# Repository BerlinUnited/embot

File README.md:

# embot
A simple controller kit for robotic experiments in embodyment. 

Some robots build by the students in our Embodied Robotics class:  
https://www.youtube.com/watch?v=9PvMIzAKYXQ

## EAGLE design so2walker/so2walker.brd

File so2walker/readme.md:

# BOM

## PCB mount

| Part  | Value  | Package          | Description    | Order                      |
|-------|--------|------------------|----------------|----------------------------|
| C1    | 100µF  | CPOL-EUE3.5-8    | Elko (Bulk)    | Reichelt, M-A 100U 35      |
| C2    | 100nF  | C-EU025-025X050  | Keramik Cap    | Reichelt, Z5U-2,5 100N     |
| D1,D2 |        | LED3MM           | LED            | -                          |
| R1,R2 | 1K     | R-EU_0207/7      | Resistor       | Reichelt, AG 04FTE52-1K    |
| SW    |        | SWITCH-SPSTPTH   | On/off Switch  | Reichelt, SS ESP101        |
| T1    |        | TAC_SWITCHPTH    | Tactile Switch | Reichelt, RND 210-00193    |
| P1-P4 | 10K    | TRIMPOT_UNIV     | Trimmerpotis   | Reichelt, ACP 9-SRS 10K    |
| M1-M4 |        | PINHD 2.54mm     | Pinheader 1x3  | Reichelt, MPE 087-1-003    |

Also needed:

* Arduino-Nano (or compatible)
* 2x Sockets 2.54 mm, 1X15, straight (if Arduino Nano shall not be permanently soldered)
* 2x Battery-Holder (e.g. Reichelt, HALTER 2XAAZ) + 4x AA Battery
* 4x Knob for Pots: e.g. Reichelt, ACHSE ACP 9 S
* 2-4x Micro-Servo: e.g. Conrad, 275460 - 62

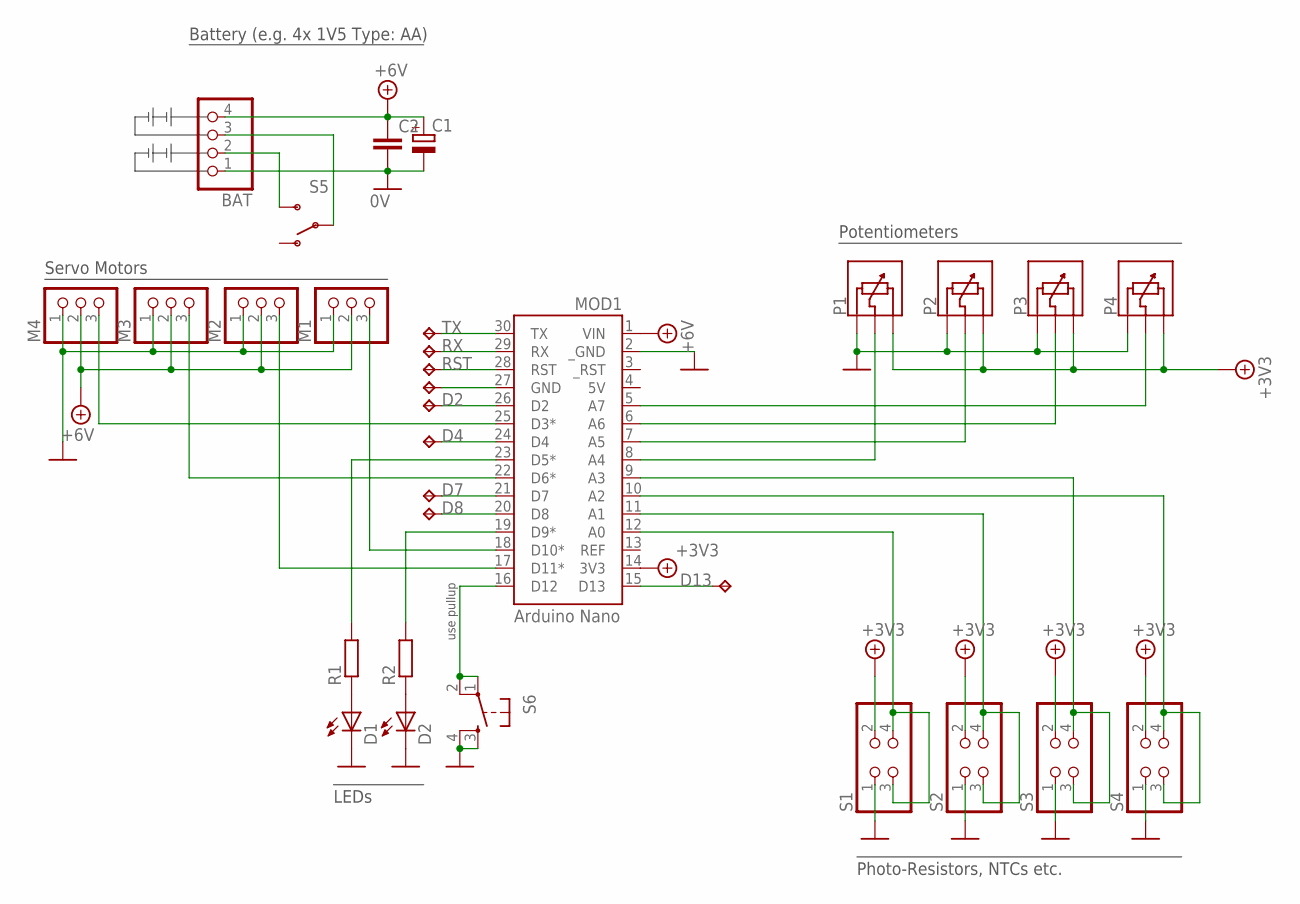
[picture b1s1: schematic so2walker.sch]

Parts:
BAT: PINHD-1X04_2.54-S; 1X04-S
C1: CPOL-EUE3.5-8; E3,5-8
C2: C-EU025-025X050; C025-025X050
D1, D2: LED3MM
M1, M2, M3, M4: PINHD-1X03_2.54-S; 1X03-S
MOD1: Arduino Nano; NANOSHLD_INV
P1, P2, P3, P4: TRIMPOT_UNIV; UNIPOT_DIL
R1, R2: R-EU_0207/7; 0207/7
S1, S2, S3, S4: PINHD-2X02_2.54; 2X02
S5: SWITCH-SPSTPTH; SWITCH-SPDT
S6: TAC_SWITCHPTH; TACTILE-PTH
TP1, TP2, TP3, TP4, TP5, TP6, TP7, TP8, TP10: TPB1,27; B1,27

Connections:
5V: MOD1.4 (5V)
+3V3: BAT.4, C1.+, C2.1, M1.2, M2.2, M3.2, M4.2, MOD1.1 (VIN), MOD1.14 (3V3), P1.3A, P1.3B, P2.3A, P2.3B, P3.3A, P3.3B, P4.3A, P4.3B, S1.2, S2.2, S3.2, S4.2
D2: MOD1.26 (D2), TP4.TP
D4: MOD1.24 (D4), TP5.TP
D7: MOD1.21 (D7), TP6.TP
D8: MOD1.20 (D8), TP7.TP
D12: MOD1.16 (D12), S6.1, S6.2
D13: MOD1.15 (D13), TP8.TP
GND: BAT.1, C1.-, C2.2, D1.K (C), D2.K (C), M1.1, M2.1, M3.1, M4.1, MOD1.2 (_GND), P1.1A, P1.1B, P2.1A, P2.1B, P3.1A, P3.1B, P4.1A, P4.1B, S1.1, S2.1, S3.1, S4.1, S6.3, S6.4
unnamed: MOD1.27 (GND), TP10.TP
unnamed: M2.3, MOD1.17 (D11*)
unnamed: M3.3, MOD1.22 (D6*)
unnamed: M4.3, MOD1.25 (D3*)
unnamed: MOD1.23 (D5*), R1.2
unnamed: MOD1.19 (D9*), R2.2
unnamed: MOD1.8 (A4), P1.2A, P1.2B
unnamed: MOD1.7 (A5), P2.2A, P2.2B
unnamed: MOD1.6 (A6), P3.2A, P3.2B
unnamed: BAT.3, S5.2
unnamed: BAT.2, S5.3 (S)
unnamed: MOD1.5 (A7), P4.2A, P4.2B
unnamed: MOD1.11 (A1), S2.3, S2.4
unnamed: MOD1.12 (A0), S1.3, S1.4
unnamed: MOD1.10 (A2), S4.3, S4.4
unnamed: MOD1.9 (A3), S3.3, S3.4
unnamed: D1.A, R1.1
unnamed: D2.A, R2.1
unnamed: M1.3, MOD1.18 (D10*)
REF: MOD1.13 (REF)
RST: MOD1.28 (RST), TP3.TP
RX: MOD1.29 (RX), TP2.TP
TX: MOD1.30 (TX), TP1.TP

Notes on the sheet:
Servo Motors
Potentiometers
Battery (e.g. 4x 1V5 Type: AA)
LEDs
Photo-Resistors, NTCs etc.
use pullup

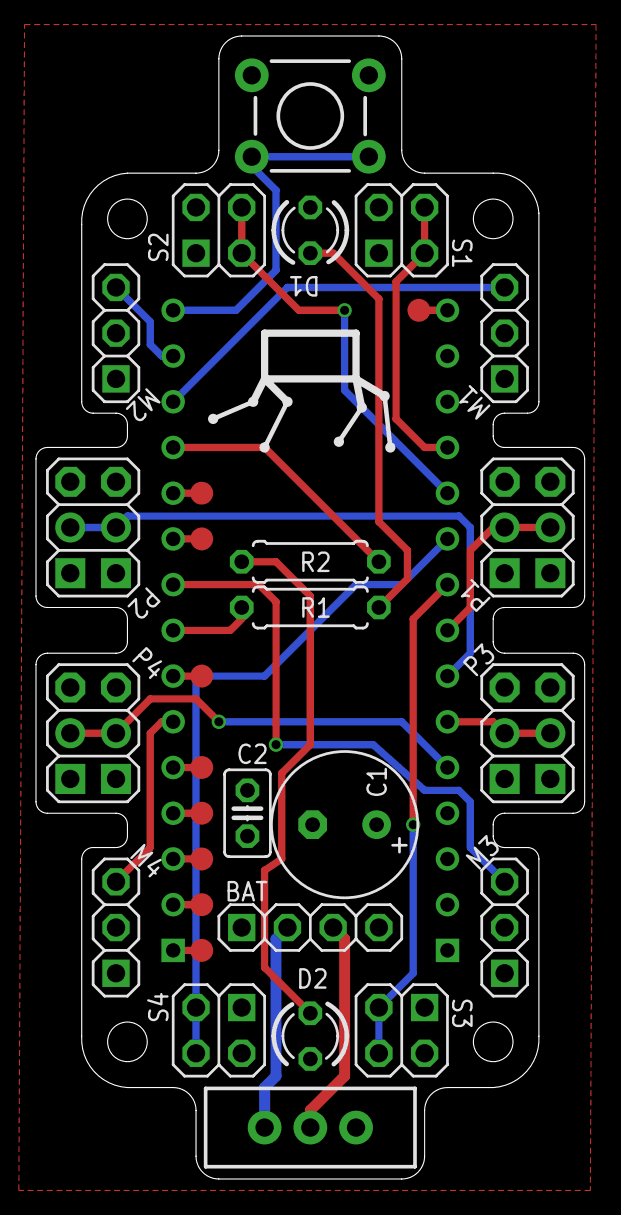
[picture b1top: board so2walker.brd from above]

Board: 2 copper layers, 30.5 x 63.5 mm, 31 parts (0 on the bottom side), 30 nets.

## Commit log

2019-02-19 copied the controller code from the original exercise repository
2019-02-19 a special readme for the first version of the robot
2019-02-19 first version of the step by step instruction for making the test board
2019-02-19 Added alternative pcb version.
2019-02-19 first draft of the component list
2019-02-19 corrected caples
2019-02-19 added missing links
2019-02-19 linebreaks
2019-03-14 Fixed bug with swapped pins, added part values, simplified routing, added complete BOM.
2019-03-14 Added a license
2019-07-24 added a link

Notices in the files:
parts and their libraries:
SparkFun: Licensing: CC v3.0 Share-Alike You are welcome to use this library for commercial purposes.
